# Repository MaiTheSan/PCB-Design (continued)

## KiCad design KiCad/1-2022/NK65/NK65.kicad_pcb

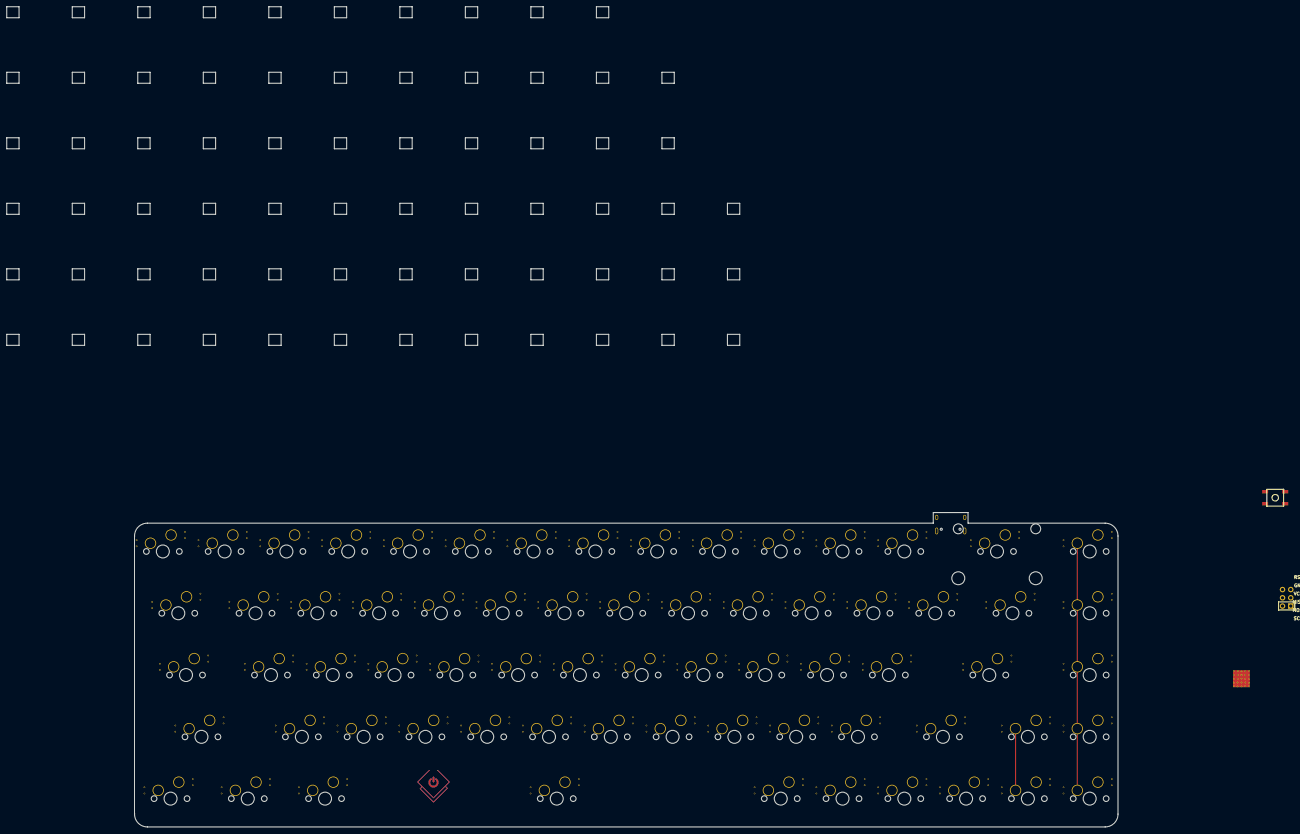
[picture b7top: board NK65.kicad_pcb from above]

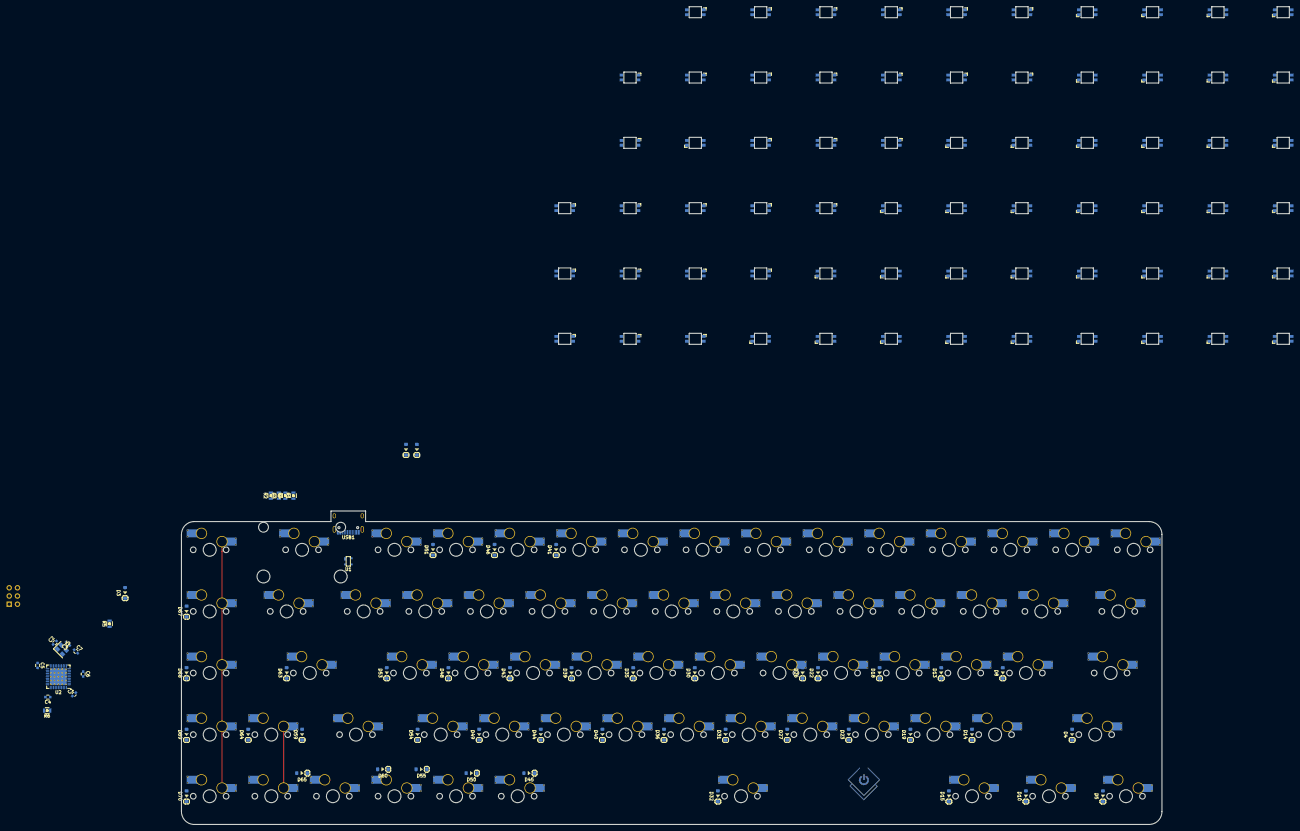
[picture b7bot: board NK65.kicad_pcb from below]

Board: 2 copper layers, 342.6 x 252.9 mm, 200 parts (129 on the bottom side), 146 nets.

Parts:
C1: 10uF; C_0603
C2, C3: 22pF; C_0603
C4, C5, C7: 0.1uF; C_0603
C6: 1uF; C_0603
D3, D4, D5, D8, D10, D13, D14, D15, D18, D19, D22, D23, D26, D27, D30, D31, D32, D33, D35, D36, D37, D39, D40, D41, D43, D44, D45, D46, D48, D49, D50, D51, D53, D54, D55, D59, D60, D63, D64, D65, D67, D68, D69, D70: D; D_SOD-123
LOGO1: Logo_Open_Hardware_Large; sanpjxlogo-PCB-type
MX3, MX4, MX8, MX9, MX10, MX13, MX14, MX15, MX16, MX18, MX19, MX20, MX21, MX22, MX23, MX24, MX25, MX26, MX27, MX28, MX29, MX30, MX31, MX32, MX33, MX35, MX36, MX37, MX38, MX39, MX40, MX41, MX42, MX43, MX44, MX45, MX46, MX47, MX50, MX51, MX52, MX53, MX54, MX56, MX57, MX58, MX59, MX60, MX62, MX63, MX65, MX67, MX70, MX71, MX72, MX73, MX75, MX76, MX77, MX78, MX79: MX-NoLED; MXOnly-1U-Hotswap-Sawns
MX5: MX-.75; MXOnly-1U-Hotswap-Sawns
MX6: MX-2.25; MXOnly-1U-Hotswap-Sawns
MX7, MX12, MX17: MX-1.25; MXOnly-1U-Hotswap-Sawns
MX34: MX-6.25; MXOnly-1U-Hotswap-Sawns
MX80: MX-NoLED; MXOnly-2U-Hotswap-Sawns
R1, R2: 5.1k; R_0805
R3, R4: 22; R_0805
R5: 10k; R_0805
R6: 1k; R_0805
SK6812MiniE1, SK6812MiniE2, SK6812MiniE3, SK6812MiniE4, SK6812MiniE5, SK6812MiniE6, SK6812MiniE7, SK6812MiniE8, SK6812MiniE9, SK6812MiniE10, SK6812MiniE11, SK6812MiniE12, SK6812MiniE13, SK6812MiniE15, SK6812MiniE17, SK6812MiniE18, SK6812MiniE19, SK6812MiniE20, SK6812MiniE21, SK6812MiniE22, SK6812MiniE23, SK6812MiniE24, SK6812MiniE25, SK6812MiniE26, SK6812MiniE27, SK6812MiniE28, SK6812MiniE29, SK6812MiniE30, SK6812MiniE31, SK6812MiniE32, SK6812MiniE33, SK6812MiniE34, SK6812MiniE35, SK6812MiniE36, SK6812MiniE37, SK6812MiniE39, SK6812MiniE41, SK6812MiniE42, SK6812MiniE43: WS2812B; RGB-6028_FLIPPED
SK6812MiniE_F1, SK6812MiniE_F2, SK6812MiniE_F3, SK6812MiniE_F4, SK6812MiniE_F5, SK6812MiniE_F6, SK6812MiniE_F7, SK6812MiniE_F8, SK6812MiniE_F9, SK6812MiniE_F10, SK6812MiniE_F11, SK6812MiniE_F12, SK6812MiniE_F13, SK6812MiniE_F14, SK6812MiniE_F15, SK6812MiniE_F16, SK6812MiniE_F19, SK6812MiniE_F20, SK6812MiniE_F21, SK6812MiniE_F22, SK6812MiniE_F23, SK6812MiniE_F24, SK6812MiniE_F25, SK6812MiniE_F26, SK6812MiniE_F27, SK6812MiniE_F28, SK6812MiniE_F29, SK6812MiniE_F31, SK6812MiniE_F32: WS2812B; RGB-6028
SW1: SW_Push; SKQG-1155865
U1: PRTR5V0U2X; SOT143B
U2: ATmega32U4-MU; QFN-44-1EP_7x7mm_P0.5mm_EP5.2x5.2mm_ThermalVias
U3: STF202-22T1G; Reset_Pretty
USB1: HRO-TYPE-C-31-M-12; HRO-TYPE-C-31-M-12-Assembly
Y1: 16Mhz; Crystal_SMD_3225-4Pin_3.2x2.5mm

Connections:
+5V: C1.2, C4.2, C5.2, C7.2, R5.1, SK6812MiniE1.1, SK6812MiniE2.1, SK6812MiniE3.1, SK6812MiniE4.1, SK6812MiniE5.1, SK6812MiniE6.1, SK6812MiniE7.1, SK6812MiniE8.1, SK6812MiniE9.1, SK6812MiniE10.1, SK6812MiniE11.1, SK6812MiniE12.1, SK6812MiniE13.1, SK6812MiniE15.1, SK6812MiniE17.1, SK6812MiniE18.1, SK6812MiniE19.1, SK6812MiniE20.1, SK6812MiniE21.1, SK6812MiniE22.1, SK6812MiniE23.1, SK6812MiniE24.1, SK6812MiniE25.1, SK6812MiniE26.1, SK6812MiniE27.1, SK6812MiniE28.1, SK6812MiniE29.1, SK6812MiniE30.1, SK6812MiniE31.1, SK6812MiniE32.1, SK6812MiniE33.1, SK6812MiniE34.1, SK6812MiniE35.1, SK6812MiniE36.1, SK6812MiniE37.1, SK6812MiniE39.1, SK6812MiniE41.1, SK6812MiniE42.1, SK6812MiniE43.1, SK6812MiniE_F1.1, SK6812MiniE_F2.1, SK6812MiniE_F3.1, SK6812MiniE_F4.1, SK6812MiniE_F5.1, SK6812MiniE_F6.1, SK6812MiniE_F7.1, SK6812MiniE_F8.1, SK6812MiniE_F9.1, SK6812MiniE_F10.1, SK6812MiniE_F11.1, SK6812MiniE_F12.1, SK6812MiniE_F13.1, SK6812MiniE_F14.1, SK6812MiniE_F15.1, SK6812MiniE_F16.1, SK6812MiniE_F19.1, SK6812MiniE_F20.1, SK6812MiniE_F21.1, SK6812MiniE_F22.1, SK6812MiniE_F23.1, SK6812MiniE_F24.1, SK6812MiniE_F25.1, SK6812MiniE_F26.1, SK6812MiniE_F27.1, SK6812MiniE_F28.1, SK6812MiniE_F29.1, SK6812MiniE_F31.1, SK6812MiniE_F32.1, U1.4, U2.2, U2.7, U2.14, U2.24, U2.34, U2.44, U3.2, USB1.2, USB1.11
COL0: MX3.1, MX4.1, MX5.1, MX6.1, MX7.1, U2.10, U3.4
COL1: MX8.1, MX9.1, MX10.1, MX12.1, U2.29
COL2: MX13.1, MX14.1, MX15.1, MX16.1, MX17.1, U2.39
COL3: MX18.1, MX19.1, MX20.1, MX21.1, U2.32
COL4: MX22.1, MX23.1, MX24.1, MX25.1, U2.28
COL5: MX26.1, MX27.1, MX28.1, MX29.1, U2.31
COL6: MX30.1, MX31.1, MX32.1, MX33.1, MX34.1, U2.27
COL7: MX35.1, MX36.1, MX37.1, MX38.1, U2.26
COL8: MX39.1, MX40.1, MX41.1, MX42.1, U2.25
COL9: MX43.1, MX44.1, MX45.1, MX46.1, MX47.1, U2.22
COL10: MX50.1, MX51.1, MX52.1, MX53.1, MX54.1, U2.21
COL11: MX56.1, MX57.1, MX58.1, MX59.1, MX60.1, U2.20
COL12: MX62.1, MX63.1, MX65.1, MX67.1, U2.30
COL13: MX70.1, MX71.1, MX72.1, MX73.1, MX80.1, U2.19
COL14: MX75.1, MX76.1, MX77.1, MX78.1, MX79.1, U2.18
D+: R3.1, U2.4
D-: R4.1, U2.3
GND: C1.1, C2.2, C3.2, C4.1, C5.1, C6.2, C7.1, R1.1, R2.1, R6.1, SK6812MiniE1.3, SK6812MiniE2.3, SK6812MiniE3.3, SK6812MiniE4.3, SK6812MiniE5.3, SK6812MiniE6.3, SK6812MiniE7.3, SK6812MiniE8.3, SK6812MiniE9.3, SK6812MiniE10.3, SK6812MiniE11.3, SK6812MiniE12.3, SK6812MiniE13.3, SK6812MiniE15.3, SK6812MiniE17.3, SK6812MiniE18.3, SK6812MiniE19.3, SK6812MiniE20.3, SK6812MiniE21.3, SK6812MiniE22.3, SK6812MiniE23.3, SK6812MiniE24.3, SK6812MiniE25.3, SK6812MiniE26.3, SK6812MiniE27.3, SK6812MiniE28.3, SK6812MiniE29.3, SK6812MiniE30.3, SK6812MiniE31.3, SK6812MiniE32.3, SK6812MiniE33.3, SK6812MiniE34.3, SK6812MiniE35.3, SK6812MiniE36.3, SK6812MiniE37.3, SK6812MiniE39.3, SK6812MiniE41.3, SK6812MiniE42.3, SK6812MiniE43.3, SK6812MiniE_F1.3, SK6812MiniE_F2.3, SK6812MiniE_F3.3, SK6812MiniE_F4.3, SK6812MiniE_F5.3, SK6812MiniE_F6.3, SK6812MiniE_F7.3, SK6812MiniE_F8.3, SK6812MiniE_F9.3, SK6812MiniE_F10.3, SK6812MiniE_F11.3, SK6812MiniE_F12.3, SK6812MiniE_F13.3, SK6812MiniE_F14.3, SK6812MiniE_F15.3, SK6812MiniE_F16.3, SK6812MiniE_F19.3, SK6812MiniE_F20.3, SK6812MiniE_F21.3, SK6812MiniE_F22.3, SK6812MiniE_F23.3, SK6812MiniE_F24.3, SK6812MiniE_F25.3, SK6812MiniE_F26.3, SK6812MiniE_F27.3, SK6812MiniE_F28.3, SK6812MiniE_F29.3, SK6812MiniE_F31.3, SK6812MiniE_F32.3, SW1.1, U1.1, U2.5, U2.15, U2.23, U2.35, U2.43, U2.45, U3.6, USB1.1, USB1.12, USB1.13, Y1.2, Y1.4
MISO: U2.11, U3.1
unnamed: C2.1, U2.17, Y1.1
unnamed: C3.1, U2.16, Y1.3
unnamed: C6.1, U2.6
unnamed: D3.2, MX5.2
unnamed: D4.2, MX6.2
unnamed: D5.2, MX7.2
unnamed: D8.2, MX10.2
unnamed: D10.2, MX12.2
unnamed: D13.2, MX15.2
unnamed: D14.2, MX16.2
unnamed: D15.2, MX17.2
unnamed: D18.2, MX20.2
unnamed: D19.2, MX21.2
unnamed: D22.2, MX24.2
unnamed: D23.2, MX25.2
unnamed: D26.2, MX28.2
unnamed: D27.2, MX29.2
unnamed: D30.2, MX32.2
unnamed: D31.2, MX33.2
unnamed: D32.2, MX34.2
unnamed: D33.2, MX35.2
unnamed: D35.2, MX37.2
unnamed: D36.2, MX38.2
unnamed: D37.2, MX39.2
unnamed: D39.2, MX41.2
unnamed: D40.2, MX42.2
unnamed: D41.2, MX43.2
unnamed: D43.2, MX45.2
unnamed: D44.2, MX46.2
unnamed: D45.2, MX47.2
unnamed: D46.2, MX50.2
unnamed: D48.2, MX52.2
unnamed: D49.2, MX53.2
unnamed: D50.2, MX54.2
unnamed: D51.2, MX56.2
unnamed: D53.2, MX58.2
unnamed: D54.2, MX59.2
unnamed: D55.2, MX60.2
unnamed: D59.2, MX65.2
unnamed: D60.2, MX67.2
unnamed: D63.2, MX71.2
unnamed: D64.2, MX72.2
unnamed: D65.2, MX73.2
unnamed: D67.2, MX76.2
unnamed: D68.2, MX77.2
unnamed: D69.2, MX78.2
unnamed: D70.2, MX79.2
unnamed: R1.2, USB1.4
unnamed: R2.2, USB1.10
unnamed: R3.2, U1.2, USB1.6, USB1.8
unnamed: R4.2, U1.3, USB1.5, USB1.7
unnamed: R6.2, U2.33
unnamed: SK6812MiniE1.2, SK6812MiniE2.4
unnamed: SK6812MiniE2.2, SK6812MiniE3.4
unnamed: SK6812MiniE3.2, SK6812MiniE4.4
unnamed: SK6812MiniE4.2, SK6812MiniE5.4
unnamed: SK6812MiniE5.2, SK6812MiniE6.4
unnamed: SK6812MiniE6.2, SK6812MiniE7.4
unnamed: SK6812MiniE7.2, SK6812MiniE8.4
unnamed: SK6812MiniE8.2, SK6812MiniE9.4
unnamed: SK6812MiniE10.2, SK6812MiniE11.4
unnamed: SK6812MiniE9.2, SK6812MiniE10.4
unnamed: SK6812MiniE11.2, SK6812MiniE12.4
unnamed: SK6812MiniE12.2, SK6812MiniE13.4
unnamed: SK6812MiniE13.2, SK6812MiniE15.4
unnamed: SK6812MiniE15.2, SK6812MiniE17.4
unnamed: SK6812MiniE17.2, SK6812MiniE_F15.4
unnamed: SK6812MiniE18.2, SK6812MiniE19.4
unnamed: SK6812MiniE18.4, SK6812MiniE_F1.2
unnamed: SK6812MiniE19.2, SK6812MiniE20.4
unnamed: SK6812MiniE20.2, SK6812MiniE21.4
unnamed: SK6812MiniE21.2, SK6812MiniE22.4
unnamed: SK6812MiniE22.2, SK6812MiniE23.4
unnamed: SK6812MiniE23.2, SK6812MiniE24.4
unnamed: SK6812MiniE24.2, SK6812MiniE25.4
unnamed: SK6812MiniE25.2, SK6812MiniE26.4
unnamed: SK6812MiniE26.2, SK6812MiniE27.4
unnamed: SK6812MiniE27.2, SK6812MiniE28.4
unnamed: SK6812MiniE28.2, SK6812MiniE29.4
unnamed: SK6812MiniE29.2, SK6812MiniE30.4
unnamed: SK6812MiniE30.2, SK6812MiniE31.4
unnamed: SK6812MiniE31.2, SK6812MiniE_F32.4
unnamed: SK6812MiniE32.2, SK6812MiniE33.4
unnamed: SK6812MiniE32.4, SK6812MiniE_F16.2
unnamed: SK6812MiniE33.2, SK6812MiniE34.4
unnamed: SK6812MiniE34.2, SK6812MiniE35.4
unnamed: SK6812MiniE35.2, SK6812MiniE36.4
unnamed: SK6812MiniE36.2, SK6812MiniE37.4
unnamed: SK6812MiniE37.2, SK6812MiniE39.4
unnamed: SK6812MiniE39.2, SK6812MiniE41.4
unnamed: SK6812MiniE41.2, SK6812MiniE42.4
unnamed: SK6812MiniE42.2, SK6812MiniE43.4
unnamed: SK6812MiniE_F1.4, SK6812MiniE_F2.2
unnamed: SK6812MiniE_F2.4, SK6812MiniE_F3.2
unnamed: SK6812MiniE_F3.4, SK6812MiniE_F4.2
unnamed: SK6812MiniE_F4.4, SK6812MiniE_F5.2
unnamed: SK6812MiniE_F5.4, SK6812MiniE_F6.2
unnamed: SK6812MiniE_F6.4, SK6812MiniE_F7.2
unnamed: SK6812MiniE_F7.4, SK6812MiniE_F8.2
unnamed: SK6812MiniE_F8.4, SK6812MiniE_F9.2
unnamed: SK6812MiniE_F9.4, SK6812MiniE_F10.2
unnamed: SK6812MiniE_F10.4, SK6812MiniE_F11.2
unnamed: SK6812MiniE_F11.4, SK6812MiniE_F12.2
unnamed: SK6812MiniE_F12.4, SK6812MiniE_F13.2
unnamed: SK6812MiniE_F13.4, SK6812MiniE_F14.2
unnamed: SK6812MiniE_F14.4, SK6812MiniE_F15.2
unnamed: SK6812MiniE_F16.4, SK6812MiniE_F19.2
unnamed: SK6812MiniE_F19.4, SK6812MiniE_F20.2
unnamed: SK6812MiniE_F20.4, SK6812MiniE_F21.2
unnamed: SK6812MiniE_F21.4, SK6812MiniE_F22.2
unnamed: SK6812MiniE_F22.4, SK6812MiniE_F23.2
unnamed: SK6812MiniE_F23.4, SK6812MiniE_F24.2
unnamed: SK6812MiniE_F24.4, SK6812MiniE_F25.2
unnamed: SK6812MiniE_F25.4, SK6812MiniE_F26.2
unnamed: SK6812MiniE_F26.4, SK6812MiniE_F27.2
unnamed: SK6812MiniE_F27.4, SK6812MiniE_F28.2
unnamed: SK6812MiniE_F28.4, SK6812MiniE_F29.2
unnamed: SK6812MiniE_F29.4, SK6812MiniE_F31.2
unnamed: SK6812MiniE_F31.4, SK6812MiniE_F32.2
RGBLED: SK6812MiniE1.4, U2.12
ROW0: D33.1, D37.1, D41.1, D46.1, D51.1, U2.38
ROW1: D67.1, U2.37
ROW2: D3.1, D8.1, D13.1, D18.1, D22.1, D26.1, D30.1, D35.1, D39.1, D43.1, D48.1, D53.1, D63.1, D68.1, U2.41
ROW3: D4.1, D14.1, D19.1, D23.1, D27.1, D31.1, D36.1, D40.1, D44.1, D49.1, D54.1, D59.1, D64.1, D69.1, U2.40
ROW4: D5.1, D10.1, D15.1, D32.1, D45.1, D50.1, D55.1, D60.1, D65.1, D70.1, U2.9, U3.3
RST: R5.2, SW1.2, U2.13, U3.5

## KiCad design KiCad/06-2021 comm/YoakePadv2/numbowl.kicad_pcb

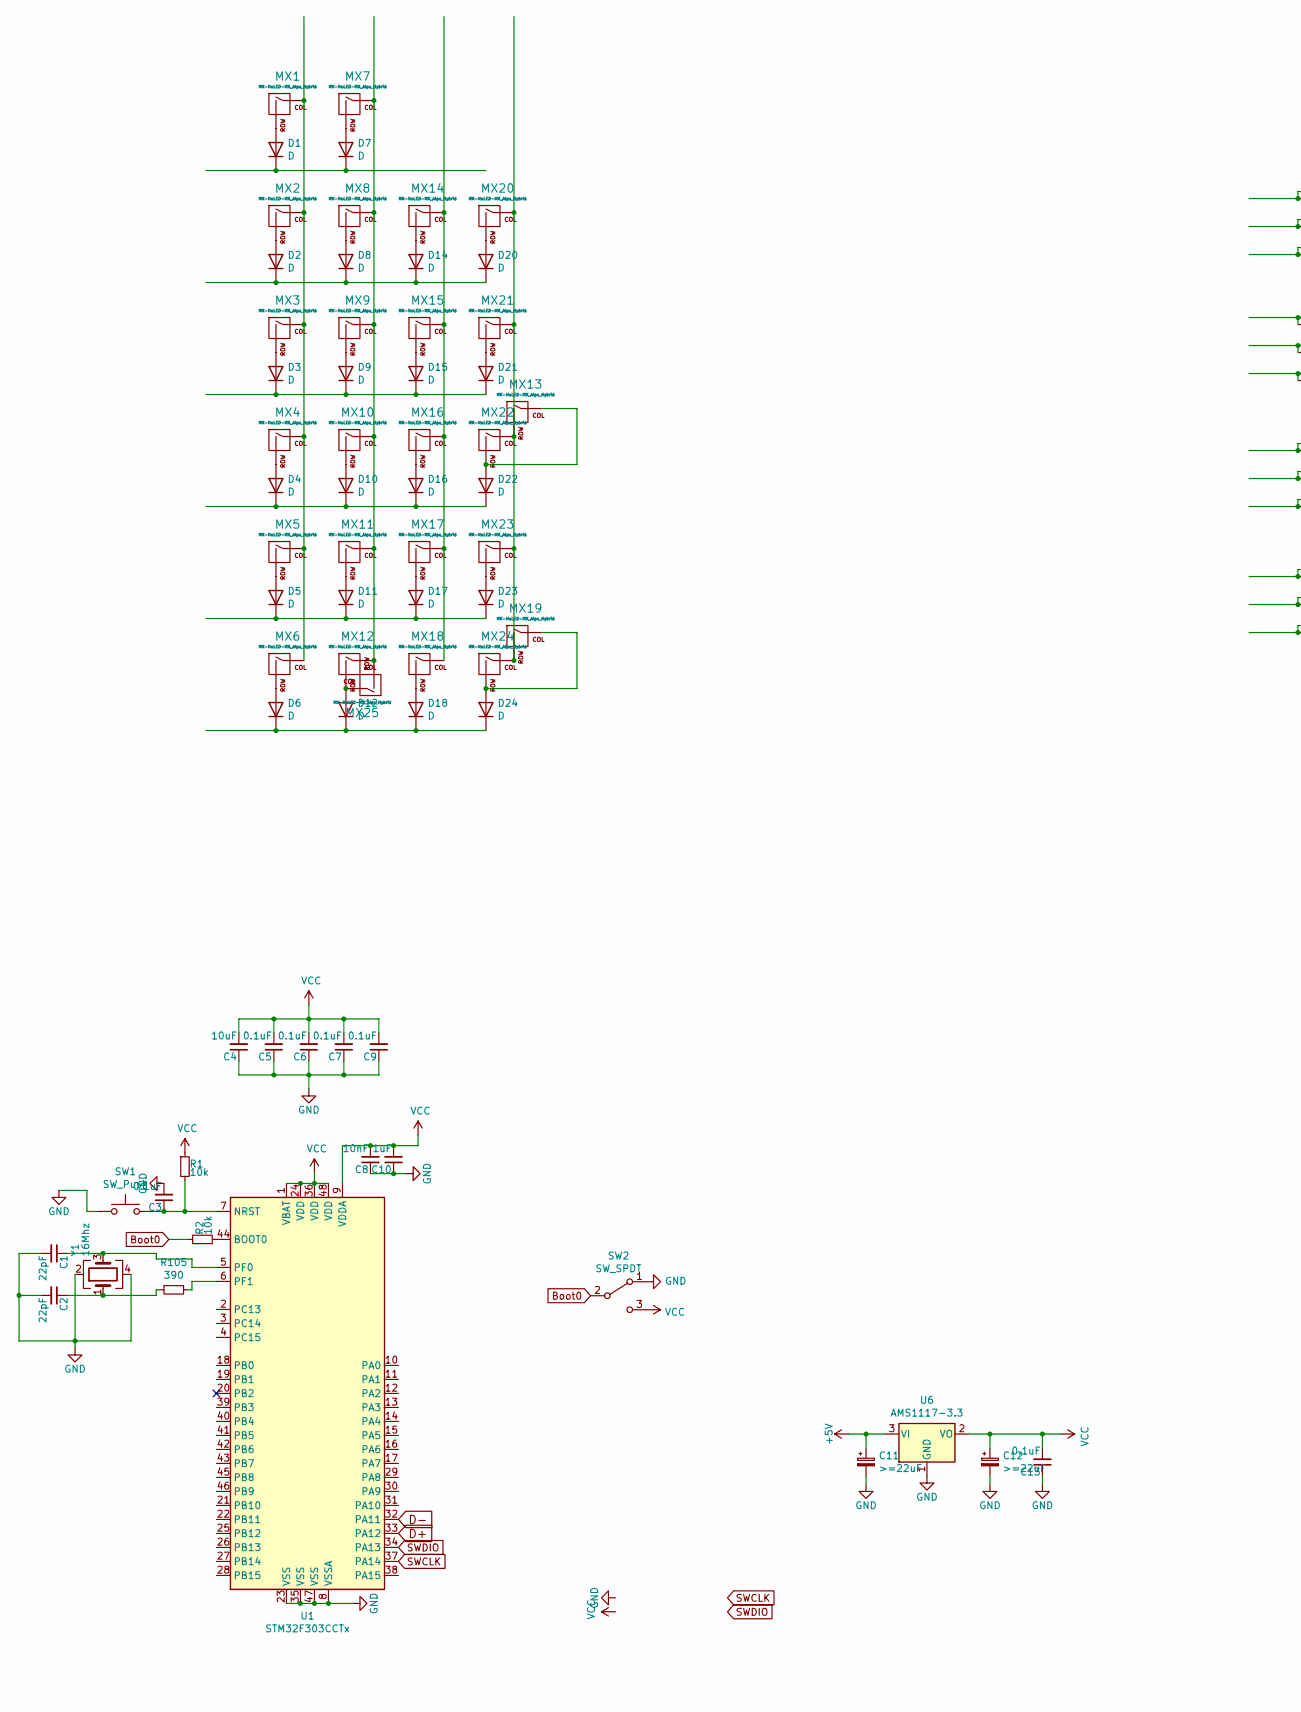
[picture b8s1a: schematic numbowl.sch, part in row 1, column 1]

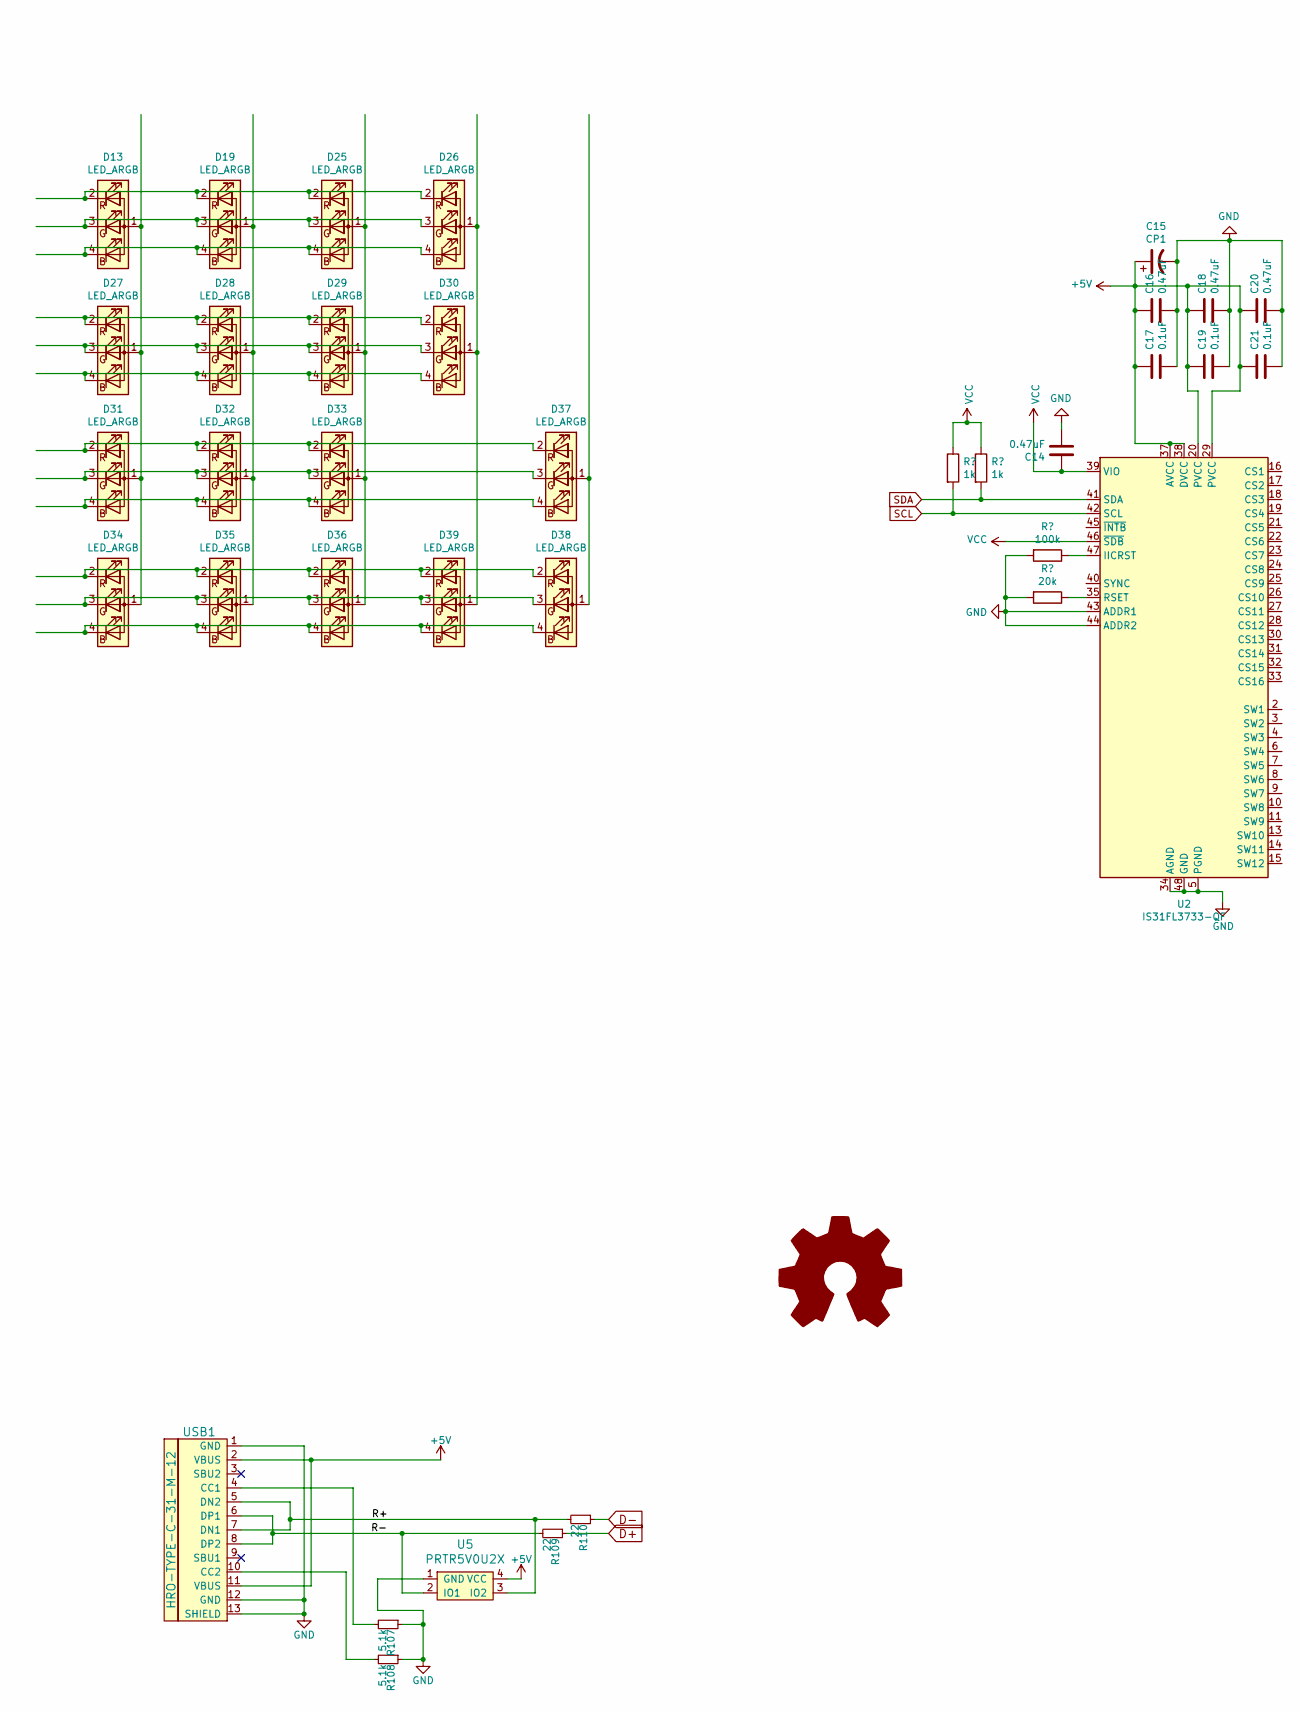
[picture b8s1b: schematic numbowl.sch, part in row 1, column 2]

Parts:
C1, C2: 22pF; C_0603
C3, C5, C6, C7, C9, C13: 0.1uF; C_0603
C4: 10uF; C_0603
C8: 10nF; C_0603
C10: 1uF; C_0603
C11, C12: >=22uF; CP_EIA-3216-12_Kemet-S
C14, C16, C18, C20: 0.47uF
C15: CP1
C17, C19, C21: 0.1uF
D1, D2, D3, D4, D5, D6, D7, D8, D9, D10, D11, D12, D14, D15, D16, D17, D18, D20, D21, D22, D23, D24: D; D_SOD-123
D13, D19, D25, D26, D27, D28, D29, D30, D31, D32, D33, D34, D35, D36, D37, D38, D39: LED_ARGB; RGB-D-6028
LOGO1: Logo_Open_Hardware_Large; sanpjxlogo
MX1, MX2, MX3, MX4, MX5, MX6, MX7, MX8, MX9, MX10, MX11, MX12, MX14, MX15, MX16, MX17, MX18, MX20, MX21, MX22, MX23, MX24: MX-NoLED-MX_Alps_Hybrid; MXOnly-1U-NoLED
MX13, MX19: MX-NoLED-MX_Alps_Hybrid; MXOnly-2U-NoLED
MX25: MX-NoLED-MX_Alps_Hybrid; MXOnly-2U-ReversedStabilizers-NoLED
R1, R2: 10k; R_0805
R105: 390; R_0805
R107, R108: 5.1k; R_0805
R109, R110: 22; R_0805
SW1: SW_Push; SKQG-1155865
SW2: SW_SPDT; SW_SPDT_PCM12
U1: STM32F303CCTx; LQFP-48_7x7mm_P0.5mm
U2: IS31FL3733-QF; QFN-48-1EP_6x6mm_P0.4mm_EP4.2x4.2mm
U5: PRTR5V0U2X; SOT143B
U6: AMS1117-3.3; SOT-223-3_TabPin2
USB1: HRO-TYPE-C-31-M-12; HRO-TYPE-C-31-M-12-Assembly
Y1: 16Mhz; Crystal_SMD_3225-4Pin_3.2x2.5mm

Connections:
+5V: C11.1, C15.1, C16.1, C17.1, C18.1, C19.1, C20.1, C21.1, U2.20 (PVCC), U2.29 (PVCC), U2.37 (AVCC), U2.38 (DVCC), U5.4 (VCC), U6.3 (VI), USB1.2 (VBUS), USB1.11 (VBUS)
/R+: R110.2, U5.3 (IO2), USB1.5 (DN2), USB1.7 (DN1)
/R-: R109.2, U5.2 (IO1), USB1.6 (DP1), USB1.8 (DP2)
Boot0: R2.1, SW2.2 (B)
D+: R109.1, U1.33 (PA12)
D-: R110.1, U1.32 (PA11)
unnamed: C1.1, U1.5 (PF0), Y1.3
unnamed: C2.1, R105.2, Y1.1
unnamed: C3.1, R1.2, SW1.2, U1.7 (NRST)
unnamed: D1.1 (K), D7.1 (K)
unnamed: D1.2 (A), MX1.2 (ROW)
unnamed: D2.2 (A), MX2.2 (ROW)
unnamed: D3.2 (A), MX3.2 (ROW)
unnamed: D4.2 (A), MX4.2 (ROW)
unnamed: D5.2 (A), MX5.2 (ROW)
unnamed: D6.2 (A), MX6.2 (ROW)
unnamed: D7.2 (A), MX7.2 (ROW)
unnamed: D8.2 (A), MX8.2 (ROW)
unnamed: D9.2 (A), MX9.2 (ROW)
unnamed: D4.1 (K), D10.1 (K), D16.1 (K), D22.1 (K)
unnamed: D10.2 (A), MX10.2 (ROW)
unnamed: D5.1 (K), D11.1 (K), D17.1 (K), D23.1 (K)
unnamed: D11.2 (A), MX11.2 (ROW)
unnamed: D6.1 (K), D12.1 (K), D18.1 (K), D24.1 (K)
unnamed: D12.2 (A), MX12.2 (ROW), MX25.1 (COL)
unnamed: D13.1 (A), D27.1 (A), D31.1 (A), D34.1 (A)
unnamed: D13.2 (RK), D19.2 (RK), D25.2 (RK), D26.2 (RK)
unnamed: D13.3 (GK), D19.3 (GK), D25.3 (GK), D26.3 (GK)
unnamed: D13.4 (BK), D19.4 (BK), D25.4 (BK), D26.4 (BK)
unnamed: D2.1 (K), D8.1 (K), D14.1 (K), D20.1 (K)
unnamed: D14.2 (A), MX14.2 (ROW)
unnamed: D3.1 (K), D9.1 (K), D15.1 (K), D21.1 (K)
unnamed: D15.2 (A), MX15.2 (ROW)
unnamed: D16.2 (A), MX16.2 (ROW)
unnamed: D17.2 (A), MX17.2 (ROW)
unnamed: D18.2 (A), MX18.2 (ROW)
unnamed: D19.1 (A), D28.1 (A), D32.1 (A), D35.1 (A)
unnamed: D20.2 (A), MX20.2 (ROW)
unnamed: D21.2 (A), MX21.2 (ROW)
unnamed: D22.2 (A), MX13.1 (COL), MX22.2 (ROW)
unnamed: D23.2 (A), MX23.2 (ROW)
unnamed: D24.2 (A), MX19.1 (COL), MX24.2 (ROW)
unnamed: D25.1 (A), D29.1 (A), D33.1 (A), D36.1 (A)
unnamed: D26.1 (A), D30.1 (A), D39.1 (A)
unnamed: D27.2 (RK), D28.2 (RK), D29.2 (RK), D30.2 (RK)
unnamed: D27.3 (GK), D28.3 (GK), D29.3 (GK), D30.3 (GK)
unnamed: D27.4 (BK), D28.4 (BK), D29.4 (BK), D30.4 (BK)
unnamed: D31.2 (RK), D32.2 (RK), D33.2 (RK), D37.2 (RK)
unnamed: D31.3 (GK), D32.3 (GK), D33.3 (GK), D37.3 (GK)
unnamed: D31.4 (BK), D32.4 (BK), D33.4 (BK), D37.4 (BK)
unnamed: D34.2 (RK), D35.2 (RK), D36.2 (RK), D38.2 (RK), D39.2 (RK)
unnamed: D34.3 (GK), D35.3 (GK), D36.3 (GK), D38.3 (GK), D39.3 (GK)
unnamed: D34.4 (BK), D35.4 (BK), D36.4 (BK), D38.4 (BK), D39.4 (BK)
unnamed: D37.1 (A), D38.1 (A)
unnamed: MX1.1 (COL), MX2.1 (COL), MX3.1 (COL), MX4.1 (COL), MX5.1 (COL), MX6.1 (COL)
unnamed: MX7.1 (COL), MX8.1 (COL), MX9.1 (COL), MX10.1 (COL), MX11.1 (COL), MX12.1 (COL), MX25.2 (ROW)
unnamed: MX13.2 (ROW), MX19.2 (ROW), MX20.1 (COL), MX21.1 (COL), MX22.1 (COL), MX23.1 (COL), MX24.1 (COL)
unnamed: MX14.1 (COL), MX15.1 (COL), MX16.1 (COL), MX17.1 (COL), MX18.1 (COL)
unnamed: R2.2, U1.44 (BOOT0)
unnamed: R105.1, U1.6 (PF1)
unnamed: R107.2, USB1.4 (CC1)
unnamed: R108.2, USB1.10 (CC2)
SWCLK: U1.37 (PA14)
SWDIO: U1.34 (PA13)

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
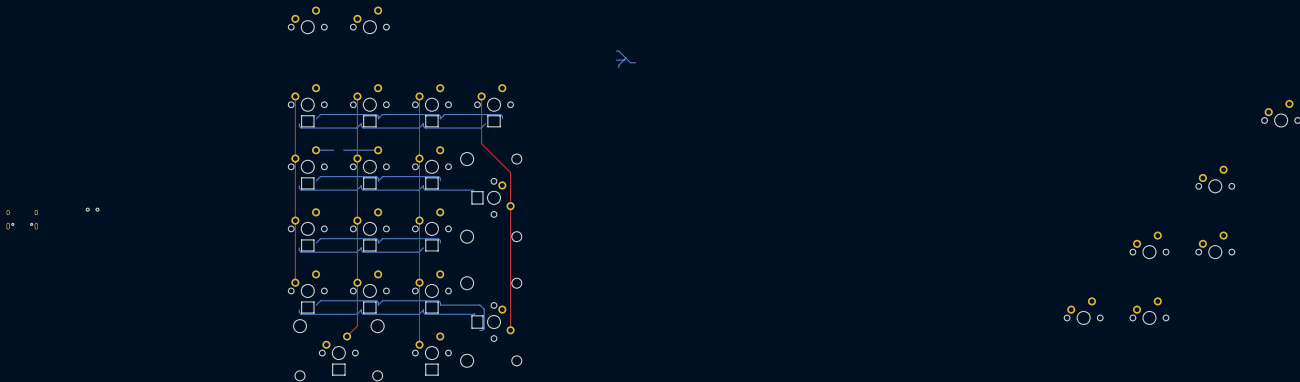
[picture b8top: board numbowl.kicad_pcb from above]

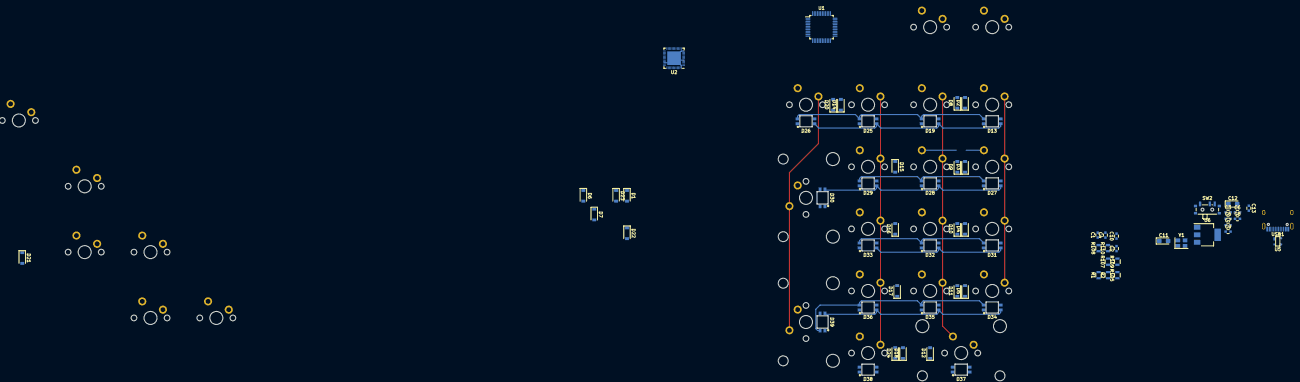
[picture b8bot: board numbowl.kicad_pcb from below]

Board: 2 copper layers, 91 parts (66 on the bottom side), 64 nets.

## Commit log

2022-11-19 Add PCB and Application
2022-11-23 Remove Useless file
2022-12-31 clean
